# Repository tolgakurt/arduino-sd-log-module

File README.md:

# arduino-sd-log-module
Arduino SD card shield that includes an external 5v-3v3 level shifter.

## The problem
Assume that you need to log some of your readings from the input pins of your Arduino Uno (or MEGA, etc.) dev board which needs to work standalone. The proper way is to store the log in an SD card connected to your board. You browse your hardware store and buy the cheapest SD card module (which is generally the LC Studio model):  

Then you find out that it has one quirk: it doesn't work when directly connected to an Arduino Uno. The reason is that SD cards operate around 3v3, but Arduino Uno GPIO pins are excited to 5v. However, these modules are still relevant because some other dev boards operate their GPIO pins with 3v3, so that this is not a problem when you use them (like an Arduino Nano, or a Rasberry Pi, or some ESP boards, etc.)   

## The solution
We need to shift the voltage of the GPIO pins from 5v to 3v3. You can pay a few extra dollars which include a level shifter. If you don't, then you need to add an external level shifter circuit. There are 3 pins that need to be shifted: CS (pin 4 on Arduino Uno dev board), MOSI (pin 11), SCK (pin 13). One of the proper ways is to use a non-inverting buffer IC. The most common IC that can do such a logic-level shifting operation is the CD4050.  

What this IC does is pretty straightforward. It should be powered with the 3v3 output pin of the Arduino Uno and it should use the same ground. Then, for example, if you feed 9th pin with a 5v signal, you will get the same signal shifted to 3v3 from 10th pin. For the pin roles, take a look at the [datasheet](https://www.futurlec.com/4000Series/CD4050.shtml).

## Circuit board
I designed the circuit in such a way that it may be installed on Arduino Uno dev boards as a shield. The layout of Uno boards is as such:  

The shield I implemented is as the following:  

The pads close to the top and bottom edges is for pins so that they correspond to the female headers of the Uno board. You can solder male pins, but if you want to stack another shield on top of this, then you need to solder female pins with long legs here. You can also omit most of the pins, for example the whole Analog IO group.  

The SD card module should be directly soldered to the PCB, if you wish to stack another shield on top of this. Using female headers in between the SD module and the shield increases height of the total assembly, which requires the upper shield to have very long legs. The pads in the middle is for an airwire. My custom CNC machine cannot etch both sides of PCBs, so these pads should be connected by a wire on top of the PCB.  

You can find the EAGLE files in the `circuit` folder. But used parts come from my custom EAGLE parts library. So, you need to have it introduced to EAGLE beforehand. The library can be downloaded [here](https://github.com/tolgakurt/eagle-parts-library).  

Here are some pictures of the built board:

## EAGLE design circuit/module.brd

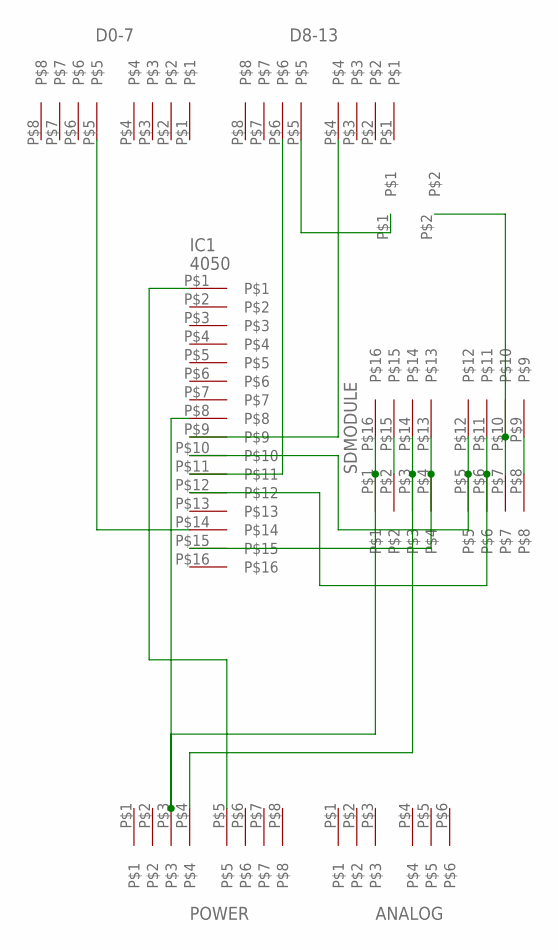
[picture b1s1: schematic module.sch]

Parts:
ANALOG: PINPLUG6PINPLUG6; PINPLUG6
D0-7, D8-13: PINPLUG8PINPLUG8; PINPLUG8
IC1: 4050; ICMOUNT16
POWER: PINPLUG8PINPLUG8; PINPLUG8
SDMODULE: PINPLUG8X2PINPLUG8X2; PINPLUG8X2
U$1: SHORTSHORT5; SHORT5

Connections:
unnamed: IC1.P$1, POWER.P$5
unnamed: D0-7.P$5, IC1.P$14
unnamed: IC1.P$12, SDMODULE.P$6, SDMODULE.P$11
unnamed: SDMODULE.P$7, SDMODULE.P$10, U$1.P$2
unnamed: D8-13.P$4, IC1.P$9
unnamed: SDMODULE.P$8, SDMODULE.P$9
unnamed: IC1.P$8, POWER.P$3, SDMODULE.P$1, SDMODULE.P$16
unnamed: D8-13.P$5, U$1.P$1
unnamed: IC1.P$15, SDMODULE.P$4, SDMODULE.P$13
unnamed: IC1.P$10, SDMODULE.P$5, SDMODULE.P$12
unnamed: D8-13.P$6, IC1.P$11
unnamed: SDMODULE.P$2, SDMODULE.P$15
unnamed: POWER.P$4, SDMODULE.P$3, SDMODULE.P$14

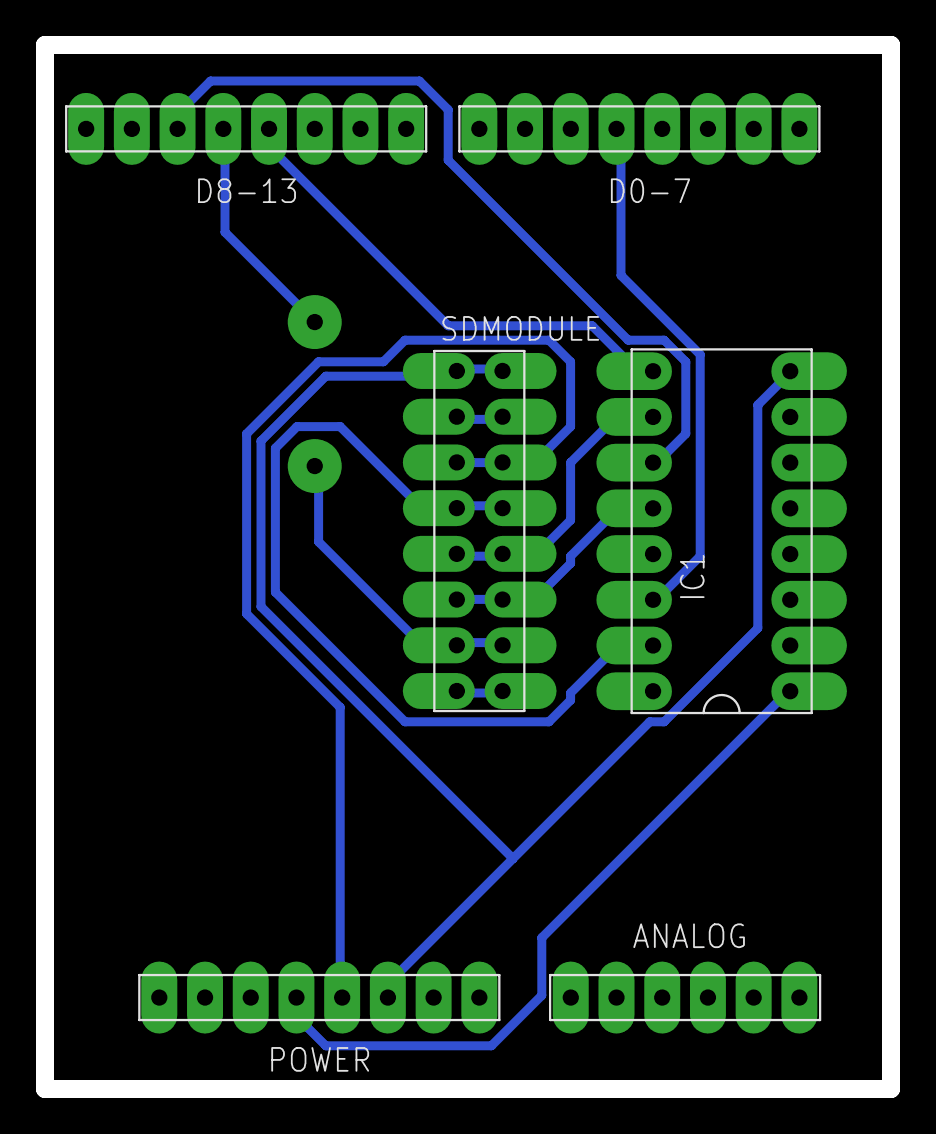
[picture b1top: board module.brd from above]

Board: 2 copper layers, 47.0 x 58.0 mm, 7 parts (0 on the bottom side), 13 nets.

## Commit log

2019-01-01 Add resource files and write instructions. Add EAGLE files.
2019-01-01 Rename a resource file.
2019-01-08 Add pictures of the built shield. Elaborate README.
2019-01-09 Move 4050 to the right side of the SD module. Remove male-female pin couples, instead use a single group of pins.
2019-01-19 Update schematic and the board. Upload latest version build pictures. Update README accordingly.
